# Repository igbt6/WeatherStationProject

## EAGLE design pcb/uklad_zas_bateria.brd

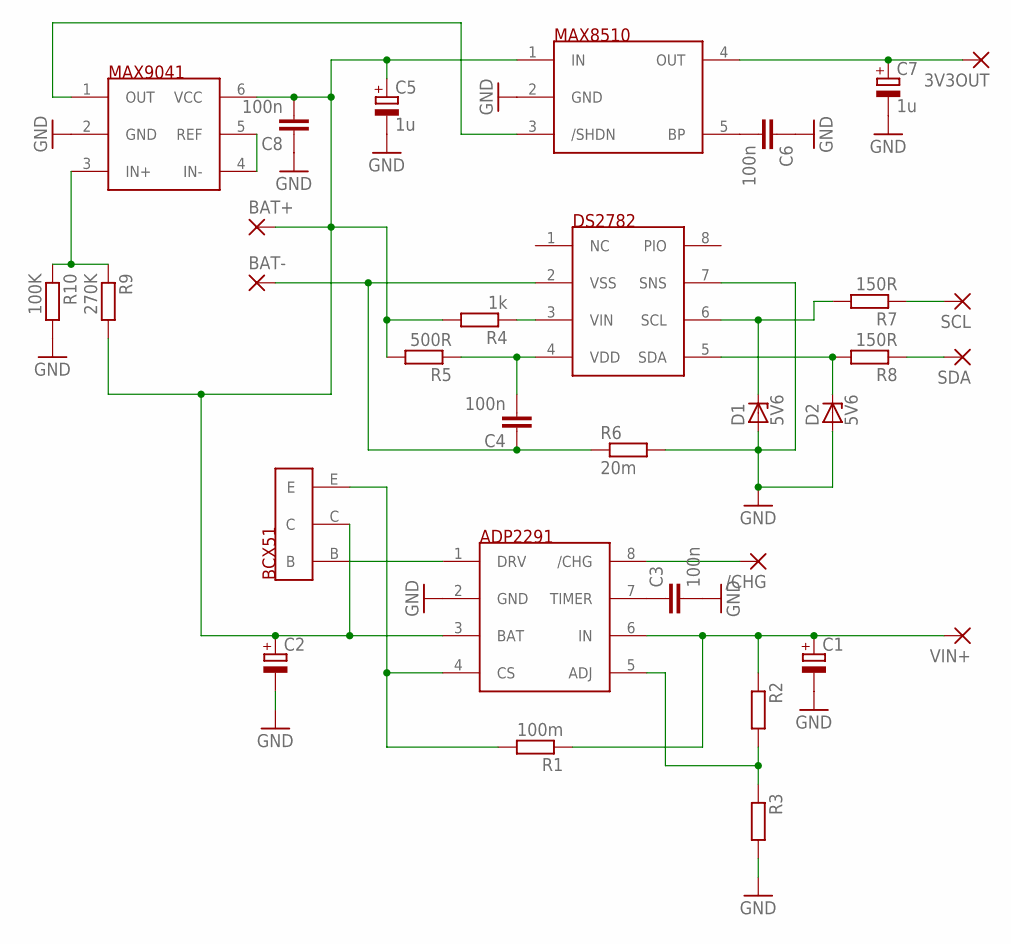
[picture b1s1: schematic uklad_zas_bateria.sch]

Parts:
3V3OUT: 2,54/0,8
/CHG: 2,54/0,8
BAT+: 2,54/0,8
BAT-: 2,54/0,8
C1, C2: CPOL-EUE2-5; E2-5
C3, C4, C6, C8: 100n; C0805
C5, C7: 1u; E2-5
D1, D2: 5V6; SOD80C
R1: 100m; 0207/10
R2, R3: R-EU_M0805; M0805
R4: 1k; M0805
R5: 500R; M0805
R6: 20m; M1206
R7, R8: 150R; M0805
R9: 270K; M0805
R10: 100K; M0805
SCL: 2,54/0,8
SDA: 2,54/0,8
U$1: ADP2291; MSOP8
U$2: BCX51; SOT89-BCE
U$3: DS2782; TSSOP8
U$4: MAX8510; SC70-5L
U$5: MAX9041; SOT23-6
VIN+: 2,54/0,8

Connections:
GND: C1.-, C2.-, C3.2, C5.-, C6.1, C7.-, C8.1, D1.A, D2.A, R3.2, R6.2, R10.2, U$1.2 (GND), U$3.7 (SNS), U$4.2 (GND), U$5.2 (GND)
unnamed: U$1.1 (DRV), U$2.B
unnamed: R1.2, U$1.4 (CS), U$2.E
unnamed: C1.+, R1.1, R2.1, U$1.6 (IN), VIN+.1
unnamed: /CHG.1, U$1.8 (/CHG)
unnamed: C6.2, U$4.5 (BP)
unnamed: C3.1, U$1.7 (TIMER)
unnamed: R2.2, R3.1, U$1.5 (ADJ)
unnamed: C4.2, R5.1, U$3.4 (VDD)
unnamed: BAT-.1, C4.1, R6.1, U$3.2 (VSS)
unnamed: R7.1, SCL.1
unnamed: R4.1, U$3.3 (VIN)
unnamed: R8.1, SDA.1
unnamed: D1.C, R7.2, U$3.6 (SCL)
unnamed: D2.C, R8.2, U$3.5 (SDA)
unnamed: U$4.3 (/SHDN), U$5.1 (OUT)
unnamed: 3V3OUT.1, C7.+, U$4.4 (OUT)
unnamed: U$5.4 (IN-), U$5.5 (REF)
unnamed: BAT+.1, C2.+, C5.+, C8.2, R4.2, R5.2, R9.2, U$1.3 (BAT), U$2.C, U$4.1 (IN), U$5.6 (VCC)
unnamed: R9.1, R10.1, U$5.3 (IN+)

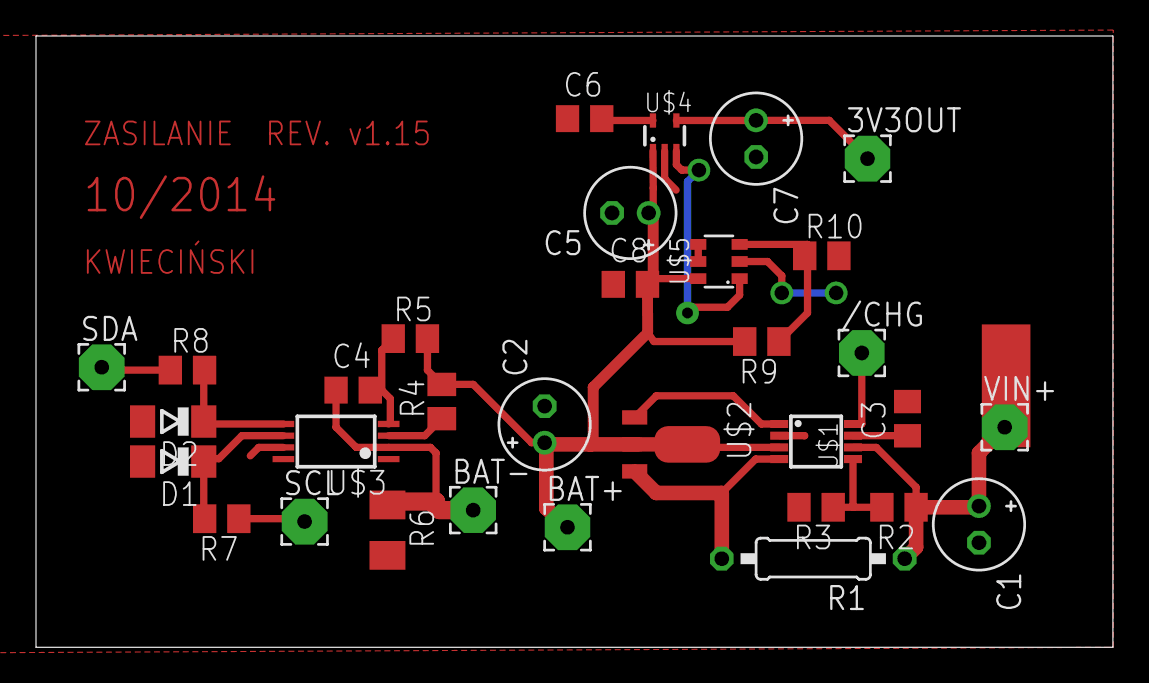
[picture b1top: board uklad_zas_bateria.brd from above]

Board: 2 copper layers, 59.8 x 34.0 mm, 32 parts (0 on the bottom side), 20 nets.
